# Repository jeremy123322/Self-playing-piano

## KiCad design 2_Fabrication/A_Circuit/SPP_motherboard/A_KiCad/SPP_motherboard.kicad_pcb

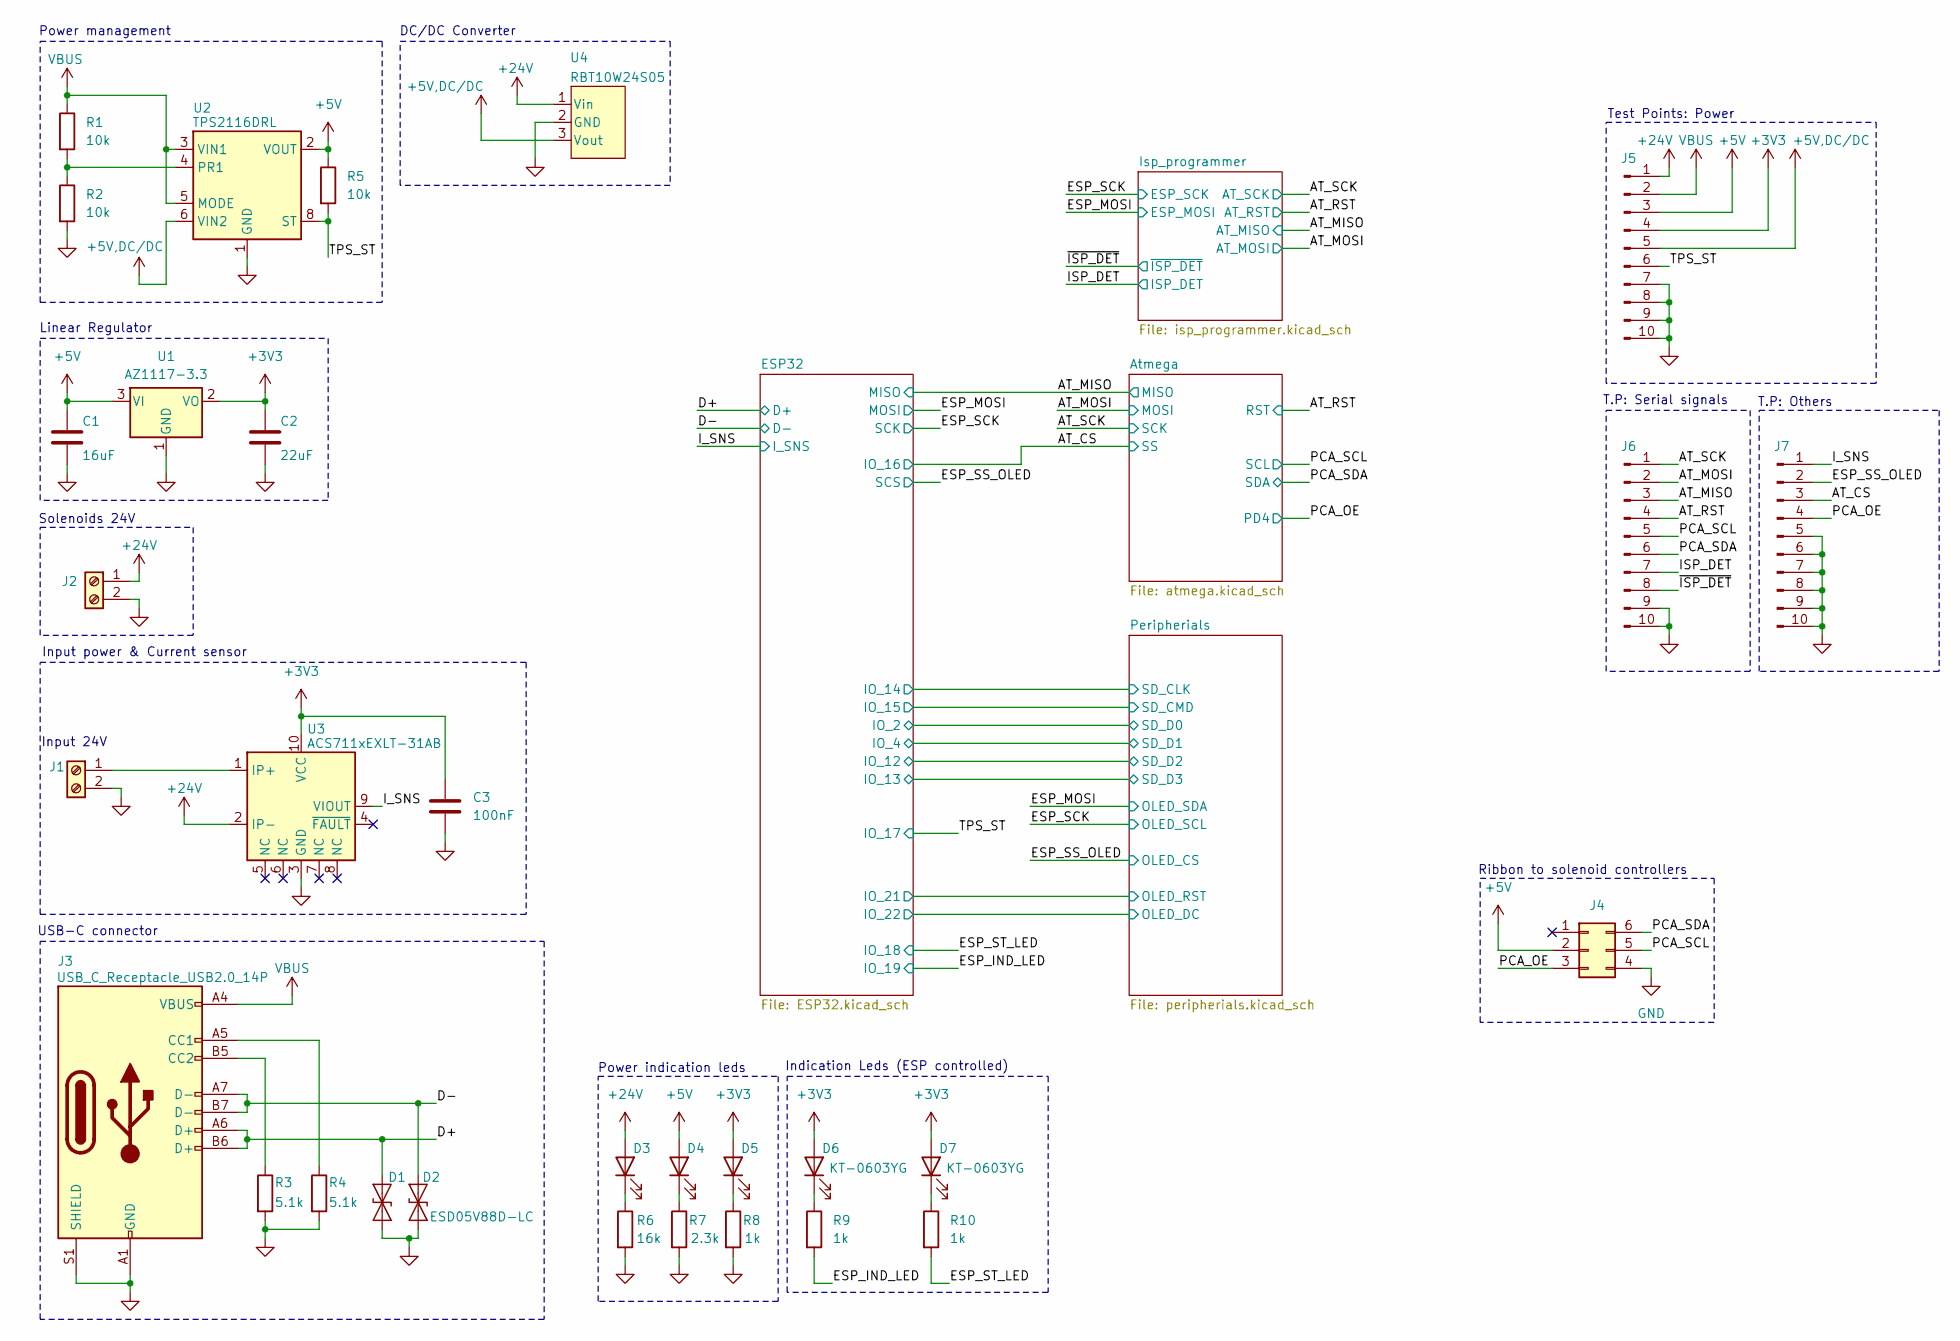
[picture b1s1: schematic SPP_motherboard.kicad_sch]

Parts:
C1: 16uF; C_0805_2012Metric
C2: 22uF; C_0805_2012Metric
C3: 100nF; C_0805_2012Metric
D1, D2: ESD05V88D-LC; D_SOD-923
D3, D4, D5, D6, D7: KT-0603YG; LED_0805_2012Metric
J1, J2: Screw_Terminal_01x02; TerminalBlock_Phoenix_MKDS-3-2-5.08_1x02_P5.08mm_Horizontal
J3: USB_C_Receptacle_USB2.0_14P; USB_C_Receptacle_HCTL_HC-TYPE-C-16P-01A
J4: Conn_02x03_Counter_Clockwise; IDC-Header_2x03_P2.54mm_Vertical
J5, J6, J7: Conn_01x10_Pin; PinHeader_1x10_P1.27mm_Vertical
R1, R2, R5: 10k; R_0805_2012Metric
R3, R4: 5.1k; R_0805_2012Metric
R6: 16k; R_0805_2012Metric
R7: 2.3k; R_0805_2012Metric
R8, R9, R10: 1k; R_0805_2012Metric
U1: AZ1117-3.3; SOT-223-3_TabPin2
U2: TPS2116DRL; SOT-583-8
U3: ACS711xEXLT-31AB; Allegro_QFN-12-10-1EP_3x3mm_P0.5mm
U4: RBT10W24S05; RBT10W24S05_XPP_XPR

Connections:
+3V3: C2.1, C3.1, D5.2 (A), D6.2 (A), D7.2 (A), J5.4, U1.2 (VO), U3.10 (VCC); also elsewhere on the board
+5V: C1.1, D4.2 (A), J4.2, J5.3, R5.1, U1.3 (VI), U2.2 (VOUT), U2.7 (VOUT); also elsewhere on the board
+5V,DC/DC: J5.5, U2.6 (VIN2), U4.3 (Vout)
+24V: D3.2 (A), J2.1, J5.1, U3.2 (IP-), U4.1 (Vin)
/AT_CS: J7.3; also elsewhere on the board
/AT_MISO: J6.3; also elsewhere on the board
/AT_MOSI: J6.2; also elsewhere on the board
/AT_RST: J6.4; also elsewhere on the board
/AT_SCK: J6.1; also elsewhere on the board
/D+: D1.2 (A2), J3.A6 (D+), J3.B6 (D+); also elsewhere on the board
/D-: D2.2 (A2), J3.A7 (D-), J3.B7 (D-); also elsewhere on the board
/ESP_IND_LED: R9.2; also elsewhere on the board
/ESP_SS_OLED: J7.2; also elsewhere on the board
/ESP_ST_LED: R10.2; also elsewhere on the board
/ISP_DET: J6.7; also elsewhere on the board
/I_SNS: J7.1, U3.9 (VIOUT); also elsewhere on the board
/PCA_OE: J4.3, J7.4; also elsewhere on the board
/PCA_SCL: J4.5, J6.5; also elsewhere on the board
/PCA_SDA: J4.6, J6.6; also elsewhere on the board
/TPS_ST: J5.6, R5.2, U2.8 (ST); also elsewhere on the board
/~ISP_DET: J6.8; also elsewhere on the board
GND: C1.2, C2.2, C3.2, D1.1 (A1), D2.1 (A1), J1.2, J2.2, J3.A1 (GND), J3.A12 (GND), J3.B1 (GND), J3.B12 (GND), J3.S1 (SHIELD), J4.4, J5.7, J5.8, J5.9, J5.10, J6.9, J6.10, J7.5, J7.6, J7.7, J7.8, J7.9, J7.10, R2.2, R3.2, R4.2, R6.2, R7.2, R8.2, U1.1 (GND), U2.1 (GND), U3.3 (GND), U4.2 (GND); also elsewhere on the board
unnamed: D3.1 (K), R6.1
unnamed: D4.1 (K), R7.1
unnamed: D5.1 (K), R8.1
unnamed: D6.1 (K), R9.1
unnamed: D7.1 (K), R10.1
unnamed: J1.1, U3.1 (IP+)
unnamed: J3.A5 (CC1), R4.1
unnamed: J3.B5 (CC2), R3.1
unnamed: R1.2, R2.1, U2.4 (PR1)
VBUS: J3.A4 (VBUS), J3.A9 (VBUS), J3.B4 (VBUS), J3.B9 (VBUS), J5.2, R1.1, U2.3 (VIN1), U2.5 (MODE); also elsewhere on the board

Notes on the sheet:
Ribbon to solenoid controllers
Input power & Current sensor
Test Points: Power
Linear Regulator
Solenoids 24V
Power management
DC/DC Converter
Indication Leds (ESP controlled)
T.P: Others
Input 24V
Power indication leds
T.P: Serial signals
USB-C connector

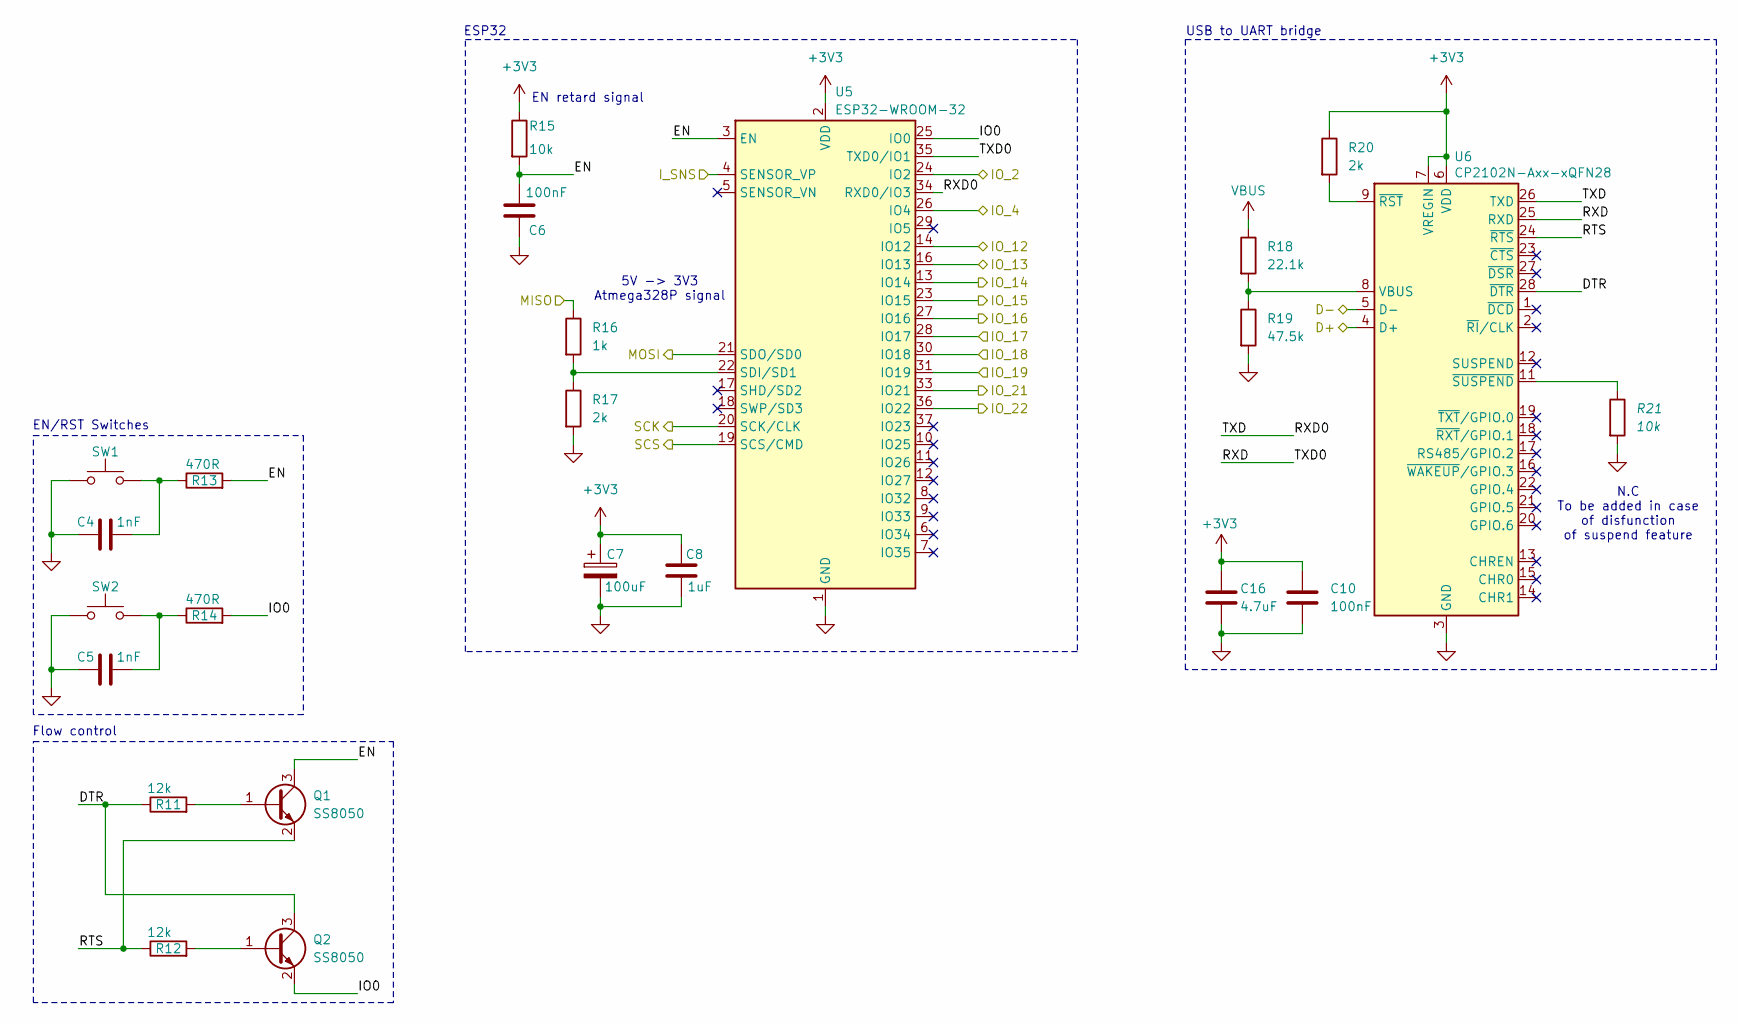
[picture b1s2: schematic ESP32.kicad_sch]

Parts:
C4, C5: 1nF; C_0805_2012Metric
C6, C10: 100nF; C_0805_2012Metric
C7: 100uF; CP_Elec_4x3
C8: 1uF; C_0805_2012Metric
C16: 4.7uF; C_0805_2012Metric
Q1, Q2: SS8050; SOT-23
R11, R12: 12k; R_0805_2012Metric
R13, R14: 470R; R_0805_2012Metric
R15, R21: 10k; R_0805_2012Metric
R16: 1k; R_0805_2012Metric
R17, R20: 2k; R_0805_2012Metric
R18: 22.1k; R_0805_2012Metric
R19: 47.5k; R_0805_2012Metric
SW1, SW2: SW_Push; C7200477
U5: ESP32-WROOM-32
U6: CP2102N-Axx-xQFN28; QFN-28-1EP_5x5mm_P0.5mm_EP3.35x3.35mm

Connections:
+3V3: C7.1, C8.1, C10.1, C16.1, R15.1, R20.1, U5.2 (VDD), U6.6 (VDD), U6.7 (VREGIN); also elsewhere on the board
/AT_CS: U5.27 (IO16); also elsewhere on the board
/AT_MISO: R16.1; also elsewhere on the board
/D+: U6.4 (D+); also elsewhere on the board
/D-: U6.5 (D-); also elsewhere on the board
/ESP32/DTR: Q2.3 (C), R11.1, U6.28 (~DTR)
/ESP32/EN: C6.2, Q1.3 (C), R13.2, R15.2, U5.3 (EN)
/ESP32/IO0: Q2.2 (E), R14.2, U5.25 (IO0)
/ESP32/IO_2: U5.24 (IO2); also elsewhere on the board
/ESP32/IO_4: U5.26 (IO4); also elsewhere on the board
/ESP32/IO_12: U5.14 (IO12); also elsewhere on the board
/ESP32/IO_13: U5.16 (IO13); also elsewhere on the board
/ESP32/IO_14: U5.13 (IO14); also elsewhere on the board
/ESP32/IO_15: U5.23 (IO15); also elsewhere on the board
/ESP32/IO_21: U5.33 (IO21); also elsewhere on the board
/ESP32/IO_22: U5.36 (IO22); also elsewhere on the board
/ESP32/RTS: Q1.2 (E), R12.1, U6.24 (~RTS)
/ESP32/RXD: U5.35 (TXD0/IO1), U6.25 (RXD)
/ESP32/RXD0: U5.34 (RXD0/IO3), U6.26 (TXD)
/ESP_IND_LED: U5.31 (IO19); also elsewhere on the board
/ESP_MOSI: U5.21 (SDO/SD0); also elsewhere on the board
/ESP_SCK: U5.20 (SCK/CLK); also elsewhere on the board
/ESP_SS_OLED: U5.19 (SCS/CMD); also elsewhere on the board
/ESP_ST_LED: U5.30 (IO18); also elsewhere on the board
/I_SNS: U5.4 (SENSOR_VP); also elsewhere on the board
/TPS_ST: U5.28 (IO17); also elsewhere on the board
GND: C4.1, C5.1, C6.1, C7.2, C8.2, C10.2, C16.2, R17.2, R19.2, R21.2, SW1.1, SW2.1, U5.1 (GND), U5.15 (GND), U5.38 (GND), U5.39 (GND), U6.3 (GND), U6.29 (GND); also elsewhere on the board
unnamed: C4.2, R13.1, SW1.2
unnamed: C5.2, R14.1, SW2.2
unnamed: Q1.1 (B), R11.2
unnamed: Q2.1 (B), R12.2
unnamed: R16.2, R17.1, U5.22 (SDI/SD1)
unnamed: R18.2, R19.1, U6.8 (VBUS)
unnamed: R20.2, U6.9 (~RST)
unnamed: R21.1, U6.11 (~SUSPEND)
VBUS: R18.1; also elsewhere on the board

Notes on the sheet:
ESP32
N.C To be added in case of disfunction of suspend feature
Flow control
5V -> 3V3 Atmega328P signal
EN/RST Switches
USB to UART bridge
EN retard signal

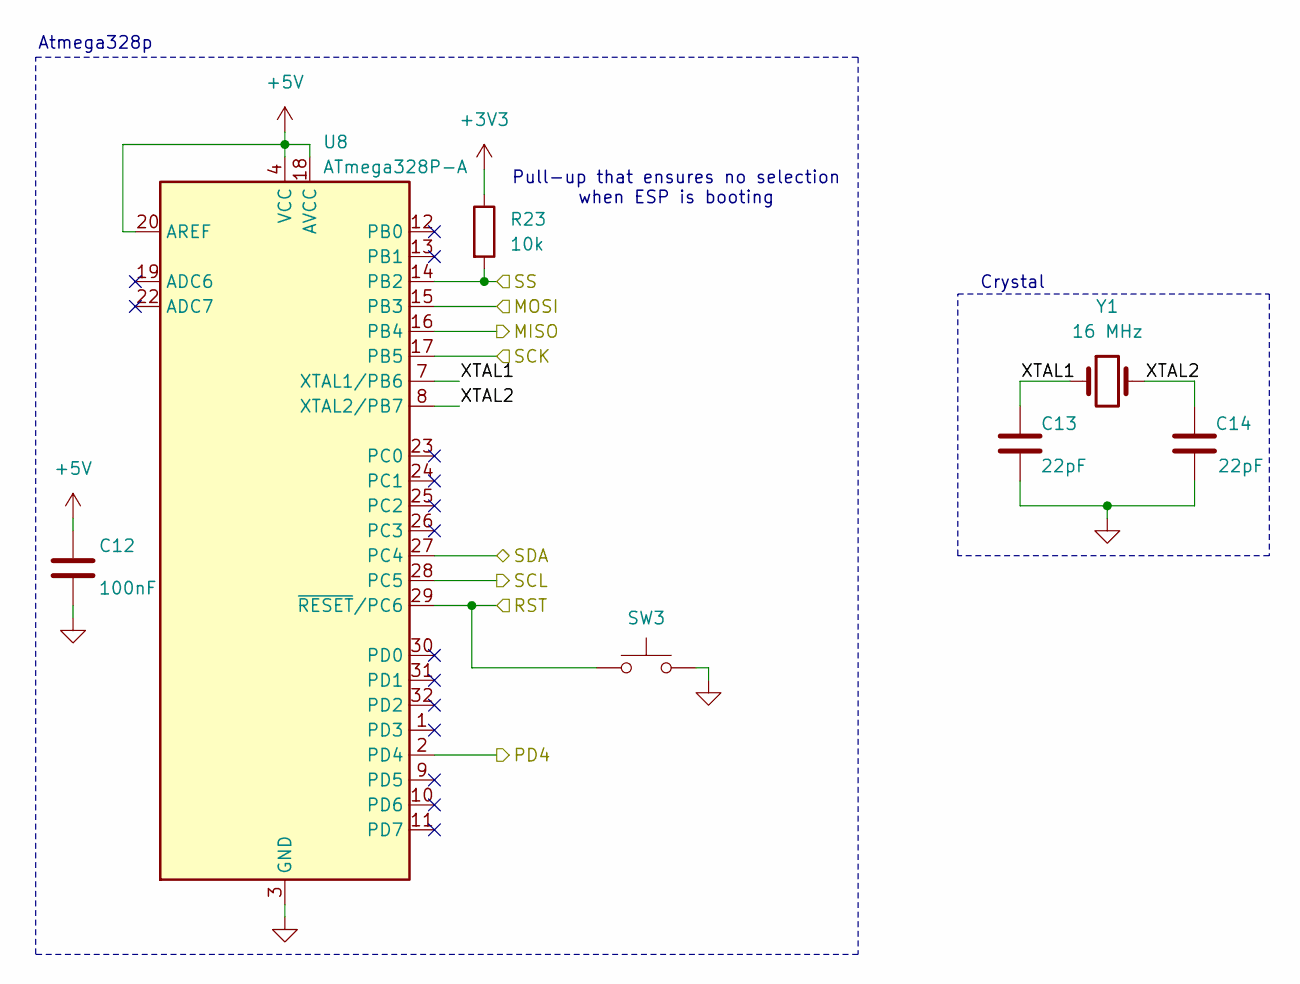
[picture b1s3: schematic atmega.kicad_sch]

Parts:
C12: 100nF; C_0805_2012Metric
C13, C14: 22pF; C_0805_2012Metric
R23: 10k; R_0805_2012Metric
SW3: SW_Push; C7200477
U8: ATmega328P-A; TQFP-32_7x7mm_P0.8mm
Y1: 16 MHz; Crystal_SMD_5032-2Pin_5.0x3.2mm

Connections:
+3V3: R23.1; also elsewhere on the board
+5V: C12.1, U8.4 (VCC), U8.6 (VCC), U8.18 (AVCC), U8.20 (AREF); also elsewhere on the board
/AT_CS: R23.2, U8.14 (PB2); also elsewhere on the board
/AT_MISO: U8.16 (PB4); also elsewhere on the board
/AT_MOSI: U8.15 (PB3); also elsewhere on the board
/AT_RST: SW3.1, U8.29 (~RESET/PC6); also elsewhere on the board
/AT_SCK: U8.17 (PB5); also elsewhere on the board
/Atmega/XTAL1: C13.1, U8.7 (XTAL1/PB6), Y1.1
/Atmega/XTAL2: C14.1, U8.8 (XTAL2/PB7), Y1.2
/PCA_OE: U8.2 (PD4); also elsewhere on the board
/PCA_SCL: U8.28 (PC5); also elsewhere on the board
/PCA_SDA: U8.27 (PC4); also elsewhere on the board
GND: C12.2, C13.2, C14.2, SW3.2, U8.3 (GND), U8.5 (GND), U8.21 (GND); also elsewhere on the board

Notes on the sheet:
Crystal
Pull-up that ensures no selection when ESP is booting
Atmega328p

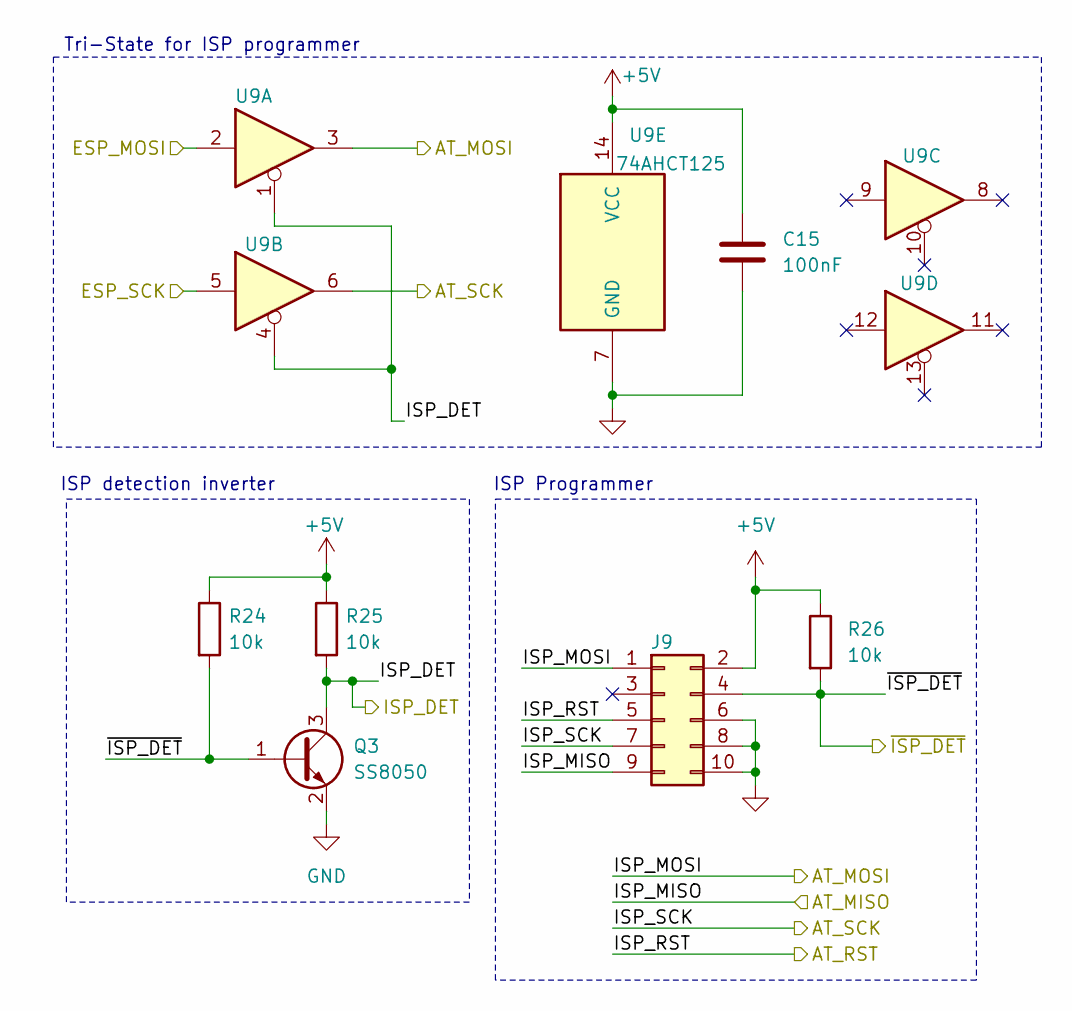
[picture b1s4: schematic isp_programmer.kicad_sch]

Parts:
C15: 100nF; C_0805_2012Metric
J9: Conn_02x05_Odd_Even; IDC-Header_2x05_P2.54mm_Vertical
Q3: SS8050; SOT-23
R24, R25, R26: 10k; R_0805_2012Metric
U9: 74AHCT125; SOIC-14_3.9x8.7mm_P1.27mm

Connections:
+5V: C15.1, J9.2, R24.1, R25.1, R26.1, U9.14 (VCC); also elsewhere on the board
/AT_MISO: J9.9; also elsewhere on the board
/AT_MOSI: J9.1, U9.3; also elsewhere on the board
/AT_RST: J9.5; also elsewhere on the board
/AT_SCK: J9.7, U9.6; also elsewhere on the board
/ESP_MOSI: U9.2; also elsewhere on the board
/ESP_SCK: U9.5; also elsewhere on the board
/ISP_DET: Q3.3 (C), R25.2, U9.1, U9.4; also elsewhere on the board
/~ISP_DET: J9.4, Q3.1 (B), R24.2, R26.2; also elsewhere on the board
GND: C15.2, J9.6, J9.8, J9.10, Q3.2 (E), U9.7 (GND); also elsewhere on the board

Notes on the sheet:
Tri-State for ISP programmer
ISP Programmer
ISP detection inverter

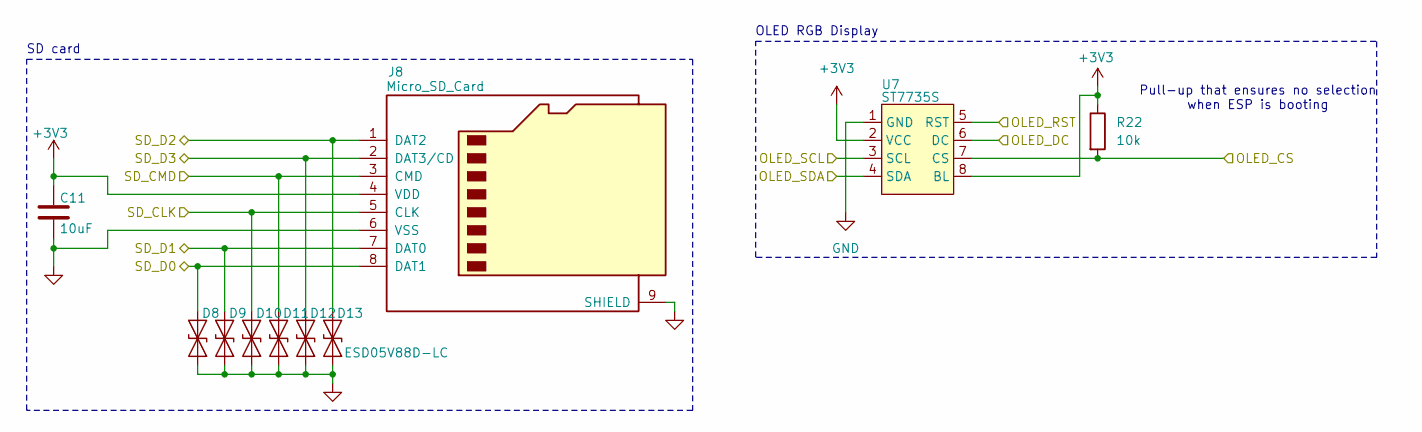
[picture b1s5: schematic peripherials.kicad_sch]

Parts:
C11: 10uF; C_0805_2012Metric
D8, D9, D10, D11, D12, D13: ESD05V88D-LC; D_SOD-923
J8: Micro_SD_Card; CUI_MSD-1-A
R22: 10k; R_0805_2012Metric
U7: ST7735S

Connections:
+3V3: C11.1, J8.4 (VDD), R22.1, U7.2 (VCC), U7.8 (BL); also elsewhere on the board
/ESP32/IO_2: D8.2 (A2), J8.8 (DAT1); also elsewhere on the board
/ESP32/IO_4: D9.2 (A2), J8.7 (DAT0); also elsewhere on the board
/ESP32/IO_12: D13.2 (A2), J8.1 (DAT2); also elsewhere on the board
/ESP32/IO_13: D12.2 (A2), J8.2 (DAT3/CD); also elsewhere on the board
/ESP32/IO_14: D10.2 (A2), J8.5 (CLK); also elsewhere on the board
/ESP32/IO_15: D11.2 (A2), J8.3 (CMD); also elsewhere on the board
/ESP32/IO_21: U7.5 (RST); also elsewhere on the board
/ESP32/IO_22: U7.6 (DC); also elsewhere on the board
/ESP_MOSI: U7.4 (SDA); also elsewhere on the board
/ESP_SCK: U7.3 (SCL); also elsewhere on the board
/ESP_SS_OLED: R22.2, U7.7 (CS); also elsewhere on the board
GND: C11.2, D8.1 (A1), D9.1 (A1), D10.1 (A1), D11.1 (A1), D12.1 (A1), D13.1 (A1), J8.6 (VSS), J8.9 (SHIELD), U7.1 (GND); also elsewhere on the board

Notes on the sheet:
Pull-up that ensures no selection when ESP is booting
OLED RGB Display
SD card

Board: 4 copper layers, 79 parts (0 on the bottom side), 58 nets, no tracks yet.

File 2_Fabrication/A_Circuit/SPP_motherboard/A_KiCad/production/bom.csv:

Designator,Footprint,Quantity,Value,LCSC Part #
"C1, C14",0805,2,10uF,
"C10, C11, C15, C3, C6",0805,5,100nF,
"C12, C13",0805,2,22pF,
C2,CP_Elec_4x3,1,22uF,
"C4, C5",0805,2,1nF,
C7,CP_Elec_4x3,1,100uF,
C8,0805,1,1uF,
C9,0805,1,4.7uF,
"D1, D10, D11, D12, D13, D2, D8, D9",D_SOD-923,8,ESD05V88D-LC,
"D3, D4, D5, D6, D7",0805,5,KT-0603YG,
J3,USB_C_Receptacle_HRO_TYPE-C-31-M-17,1,USB_C_Receptacle_USB2.0_14P,
J4,IDC-Header_2x03_P2.54mm_Vertical,1,Conn_02x03_Counter_Clockwise,
"J5, J6, J7",PinHeader_1x10_P1.27mm_Vertical,3,Conn_01x10_Pin,
J8,CUI_MSD-1-A,1,Micro_SD_Card,
J9,IDC-Header_2x05_P2.54mm_Vertical,1,Conn_02x05_Odd_Even,
"Q1, Q2, Q3",SOT-23,3,SS8050,
"R1, R15, R2, R21, R22, R23, R24, R25, R26, R5",0805,10,10k,
"R10, R16, R8, R9",0805,4,1k,
"R11, R12",0805,2,12k,
"R13, R14",0805,2,470R,
"R17, R20",0805,2,2k,
R18,0805,1,22.1k,
R19,0805,1,47.5k,
"R3, R4",0805,2,5.1k,
R6,0805,1,16k,
R7,0805,1,2.3k,
"SW1, SW2, SW3",C7200477,3,SW_Push,
U1,SOT-223-3_TabPin2,1,AZ1117-3.3,
U2,SOT-583-8,1,TPS2116DRL,
U3,Allegro_QFN-12-10-1EP_3x3mm_P0.5mm,1,ACS711xEXLT-31AB,
U4,RBT10W24S05_XPP_XPR,1,RBT10W24S05,
U5,ESP32-WROOM-32,1,ESP32-WROOM-32,
U6,QFN-28-1EP_5x5mm_P0.5mm_EP3.35x3.35mm,1,CP2102N-Axx-xQFN28,
U7,TQFP-32_7x7mm_P0.8mm,1,ATmega328P-A,
U8,ST7735S,1,ST7735S,
U9,SOIC-14_3.9x8.7mm_P1.27mm,1,74AHCT125,
Y1,Crystal_SMD_5032-2Pin_5.0x3.2mm,1,16 MHz,

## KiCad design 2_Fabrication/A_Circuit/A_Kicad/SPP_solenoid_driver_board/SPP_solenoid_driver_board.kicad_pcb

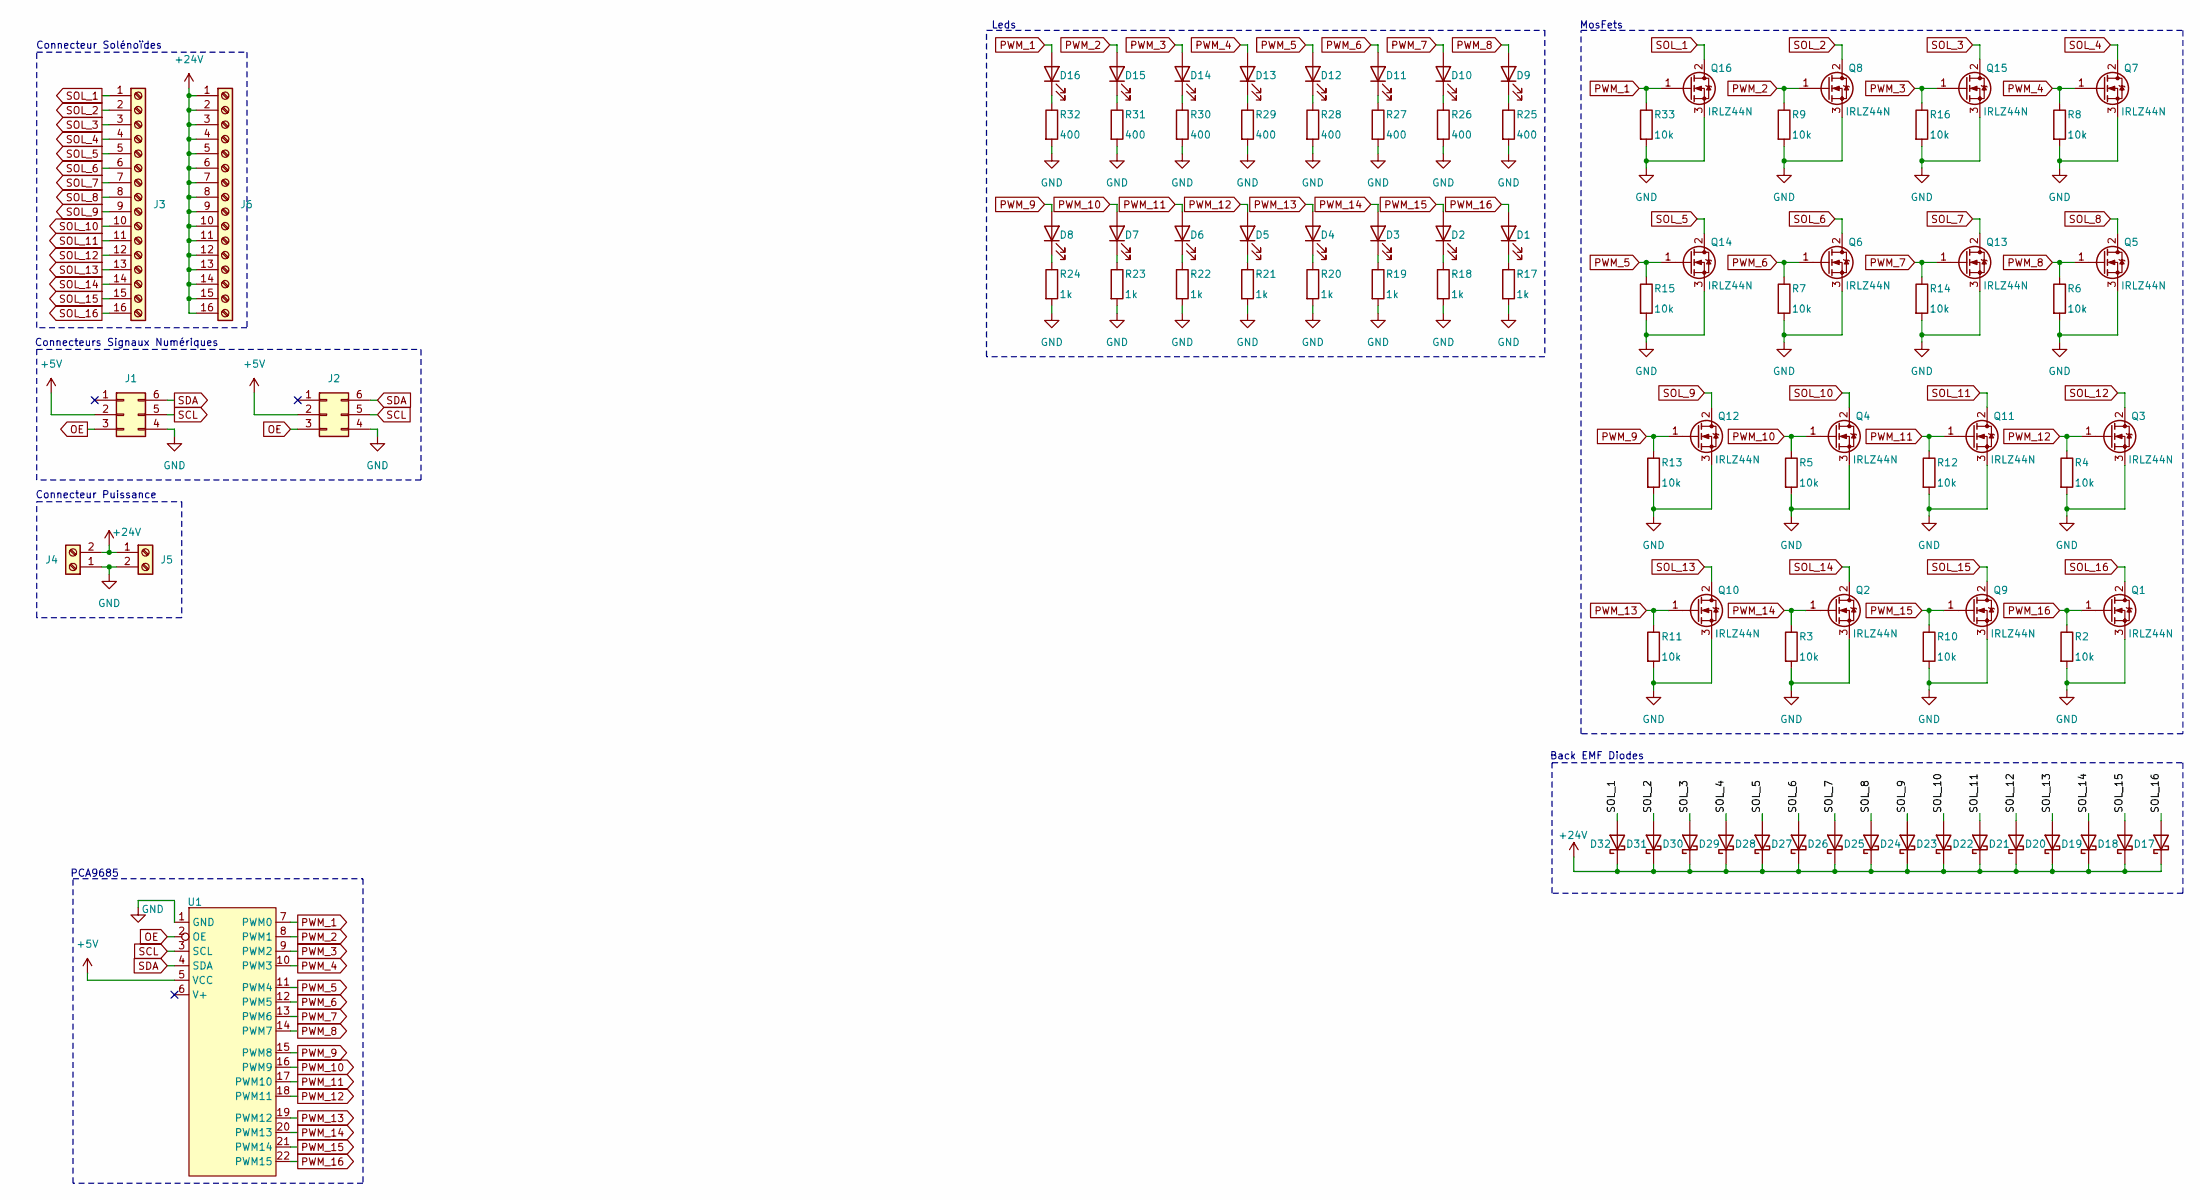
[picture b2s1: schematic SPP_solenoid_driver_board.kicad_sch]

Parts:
D1, D2, D3, D4, D5, D6, D7, D8, D9, D10, D11, D12, D13, D14, D15, D16: LED; LED_D5.0mm_Clear
D17, D18, D19, D20, D21, D22, D23, D24, D25, D26, D27, D28, D29, D30, D31, D32: 1N5819; D_DO-41_SOD81_P10.16mm_Horizontal
J1, J2: Conn_02x03_Counter_Clockwise; IDC-Header_2x03_P2.54mm_Vertical
J3, J6: Screw_Terminal_01x16; TerminalBlock_Phoenix_PT-1,5-16-5.0-H_1x16_P5.00mm_Horizont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
J4, J5: Screw_Terminal_01x02; TerminalBlock_Phoenix_MKDS-1,5-2_1x02_P5.00mm_Horizontal
Q1, Q2, Q3, Q4, Q5, Q6, Q7, Q8, Q9, Q10, Q11, Q12, Q13, Q14, Q15, Q16: IRLZ44N; TO-220-3_Vertical
R2, R3, R4, R5, R6, R7, R8, R9, R10, R11, R12, R13, R14, R15, R16, R33: 10k; R_1206_3216Metric
R17, R18, R19, R20, R21, R22, R23, R24: 1k; R_1206_3216Metric
R25, R26, R27, R28, R29, R30, R31, R32: 400; R_1206_3216Metric
U1: PCA9685_Devkit

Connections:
+5V: J1.2, J2.2, U1.5 (VCC)
+24V: D17.1 (K), D18.1 (K), D19.1 (K), D20.1 (K), D21.1 (K), D22.1 (K), D23.1 (K), D24.1 (K), D25.1 (K), D26.1 (K), D27.1 (K), D28.1 (K), D29.1 (K), D30.1 (K), D31.1 (K), D32.1 (K), J4.2, J5.1, J6.1, J6.2, J6.3, J6.4, J6.5, J6.6, J6.7, J6.8, J6.9, J6.10, J6.11, J6.12, J6.13, J6.14, J6.15, J6.16
GND: J1.4, J2.4, J4.1, J5.2, Q1.3 (S), Q2.3 (S), Q3.3 (S), Q4.3 (S), Q5.3 (S), Q6.3 (S), Q7.3 (S), Q8.3 (S), Q9.3 (S), Q10.3 (S), Q11.3 (S), Q12.3 (S), Q13.3 (S), Q14.3 (S), Q15.3 (S), Q16.3 (S), R2.2, R3.2, R4.2, R5.2, R6.2, R7.2, R8.2, R9.2, R10.2, R11.2, R12.2, R13.2, R14.2, R15.2, R16.2, R17.2, R18.2, R19.2, R20.2, R21.2, R22.2, R23.2, R24.2, R25.2, R26.2, R27.2, R28.2, R29.2, R30.2, R31.2, R32.2, R33.2, U1.1 (GND)
unnamed: D1.1 (K), R17.1
unnamed: D2.1 (K), R18.1
unnamed: D3.1 (K), R19.1
unnamed: D4.1 (K), R20.1
unnamed: D5.1 (K), R21.1
unnamed: D6.1 (K), R22.1
unnamed: D7.1 (K), R23.1
unnamed: D8.1 (K), R24.1
unnamed: D9.1 (K), R25.1
unnamed: D10.1 (K), R26.1
unnamed: D11.1 (K), R27.1
unnamed: D12.1 (K), R28.1
unnamed: D13.1 (K), R29.1
unnamed: D14.1 (K), R30.1
unnamed: D15.1 (K), R31.1
unnamed: D16.1 (K), R32.1
OE: J1.3, J2.3, U1.2 (OE)
PWM_1: D16.2 (A), Q16.1 (G), R33.1, U1.7 (PWM0)
PWM_2: D15.2 (A), Q8.1 (G), R9.1, U1.8 (PWM1)
PWM_3: D14.2 (A), Q15.1 (G), R16.1, U1.9 (PWM2)
PWM_4: D13.2 (A), Q7.1 (G), R8.1, U1.10 (PWM3)
PWM_5: D12.2 (A), Q14.1 (G), R15.1, U1.11 (PWM4)
PWM_6: D11.2 (A), Q6.1 (G), R7.1, U1.12 (PWM5)
PWM_7: D10.2 (A), Q13.1 (G), R14.1, U1.13 (PWM6)
PWM_8: D9.2 (A), Q5.1 (G), R6.1, U1.14 (PWM7)
PWM_9: D8.2 (A), Q12.1 (G), R13.1, U1.15 (PWM8)
PWM_10: D7.2 (A), Q4.1 (G), R5.1, U1.16 (PWM9)
PWM_11: D6.2 (A), Q11.1 (G), R12.1, U1.17 (PWM10)
PWM_12: D5.2 (A), Q3.1 (G), R4.1, U1.18 (PWM11)
PWM_13: D4.2 (A), Q10.1 (G), R11.1, U1.19 (PWM12)
PWM_14: D3.2 (A), Q2.1 (G), R3.1, U1.20 (PWM13)
PWM_15: D2.2 (A), Q9.1 (G), R10.1, U1.21 (PWM14)
PWM_16: D1.2 (A), Q1.1 (G), R2.1, U1.22 (PWM15)
SCL: J1.5, J2.5, U1.3 (SCL)
SDA: J1.6, J2.6, U1.4 (SDA)
SOL_1: D32.2 (A), J3.1, Q16.2 (D)
SOL_2: D31.2 (A), J3.2, Q8.2 (D)
SOL_3: D30.2 (A), J3.3, Q15.2 (D)
SOL_4: D29.2 (A), J3.4, Q7.2 (D)
SOL_5: D28.2 (A), J3.5, Q14.2 (D)
SOL_6: D27.2 (A), J3.6, Q6.2 (D)
SOL_7: D26.2 (A), J3.7, Q13.2 (D)
SOL_8: D25.2 (A), J3.8, Q5.2 (D)
SOL_9: D24.2 (A), J3.9, Q12.2 (D)
SOL_10: D23.2 (A), J3.10, Q4.2 (D)
SOL_11: D22.2 (A), J3.11, Q11.2 (D)
SOL_12: D21.2 (A), J3.12, Q3.2 (D)
SOL_13: D20.2 (A), J3.13, Q10.2 (D)
SOL_14: D19.2 (A), J3.14, Q2.2 (D)
SOL_15: D18.2 (A), J3.15, Q9.2 (D)
SOL_16: D17.2 (A), J3.16, Q1.2 (D)

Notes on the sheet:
Back EMF Diodes
MosFets
Leds
PCA9685
Connecteurs Signaux Numériques
Connecteur Puissance
Connecteur Solénoïdes

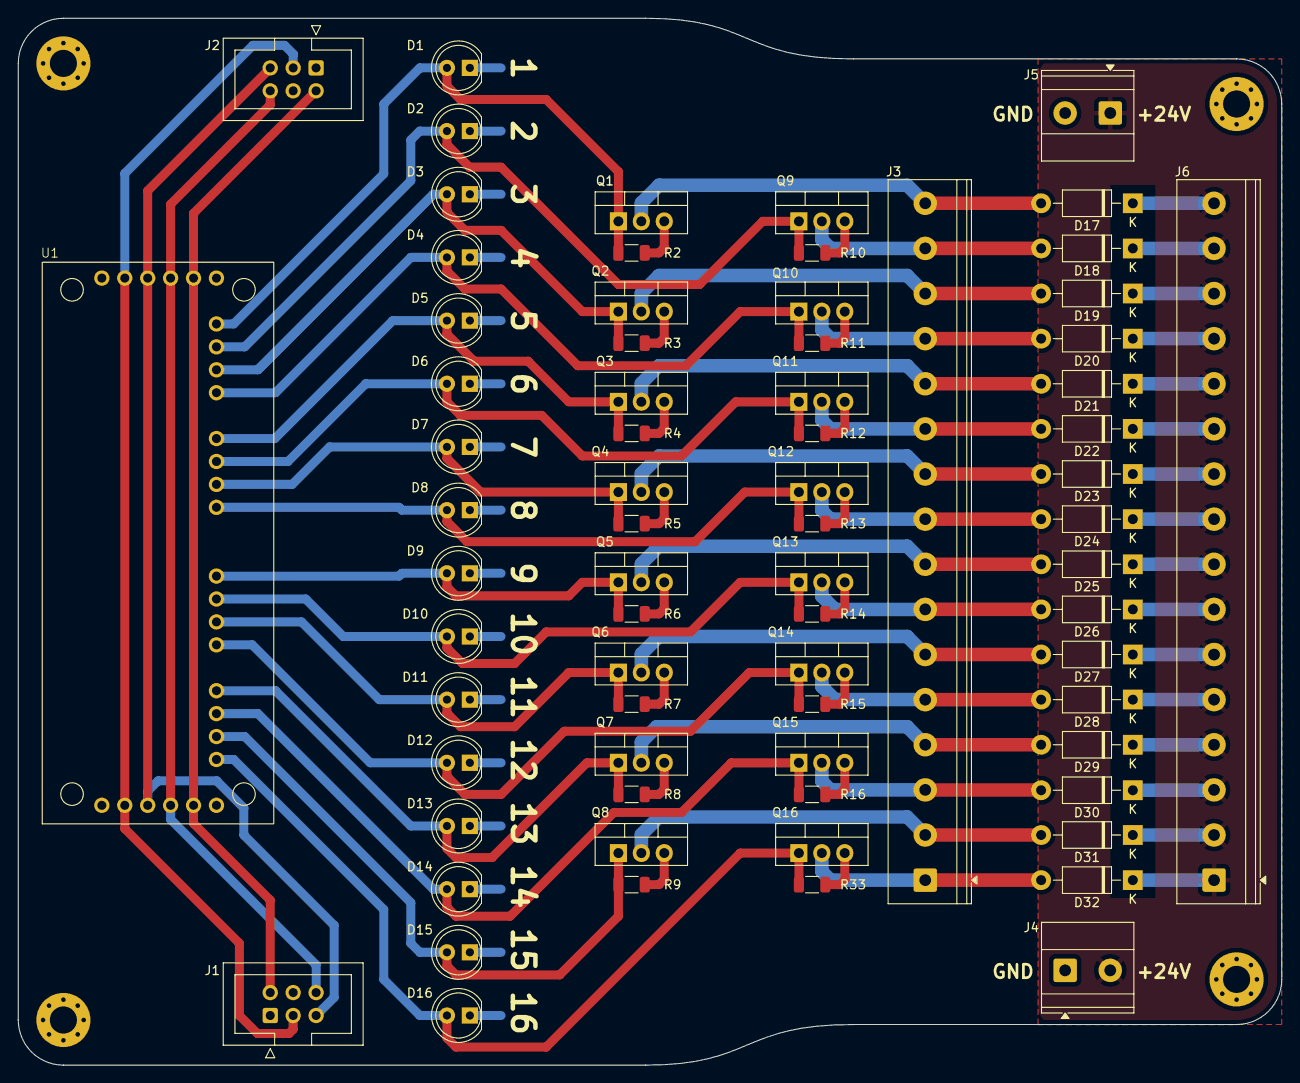
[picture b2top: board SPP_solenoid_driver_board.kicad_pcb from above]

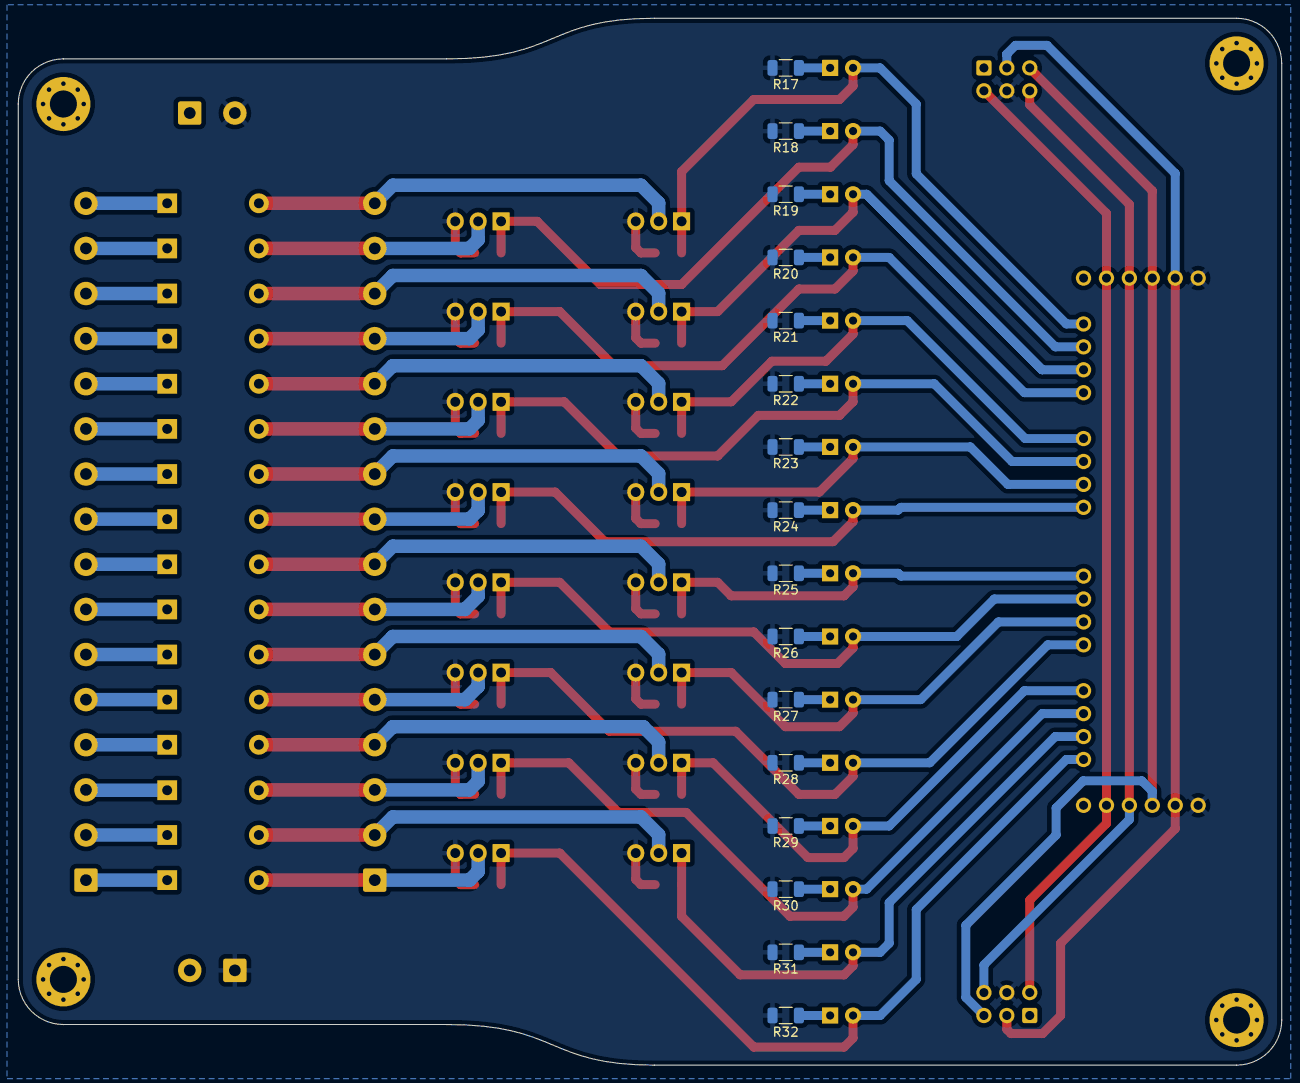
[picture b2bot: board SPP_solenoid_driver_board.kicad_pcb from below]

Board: 2 copper layers, 140.0 x 116.0 mm, 87 parts (16 on the bottom side), 54 nets.
